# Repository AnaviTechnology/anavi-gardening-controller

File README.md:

# ANAVI Gardening Controller

Open source hardware IoT gardening controller with soil moisture sensors, I2C sensors, mini OLED SSD1306 SSD display and [Seeed Studio’s XIAO RP2040 module](https://www.seeedstudio.com/XIAO-RP2040-v1-0-p-5026.html?utm_source=github&utm_medium=ANAVI&utm_campaign=Handle) that provides a USB-C connector and a Raspberry Pi RP2040 microcontroller.

ANAVI Gardening Controller has been designed with [the cross platform and open source electronics design automation suite KiCad](https://kicad.org/).

# License

The project is released under the [Creative Commons Attribution-ShareAlike 4.0 International (CC BY-SA 4.0)](https://creativecommons.org/licenses/by-sa/4.0/).

Note: This is a human-readable summary of (and not a substitute for) the [license](https://creativecommons.org/licenses/by-sa/4.0/legalcode).

You are free to:

Share — copy and redistribute the material in any medium or format Adapt — remix, transform, and build upon the material for any purpose, even commercially. The licensor cannot revoke these freedoms as long as you follow the license terms. Under the following terms:

Attribution — You must give appropriate credit, provide a link to the license, and indicate if changes were made. You may do so in any reasonable manner, but not in any way that suggests the licensor endorses you or your use. ShareAlike — If you remix, transform, or build upon the material, you must distribute your contributions under the same license as the original. No additional restrictions — You may not apply legal terms or technological measures that legally restrict others from doing anything the license permits. Notices:

You do not have to comply with the license for elements of the material in the public domain or where your use is permitted by an applicable exception or limitation. No warranties are given. The license may not give you all of the permissions necessary for your intended use. For example, other rights such as publicity, privacy, or moral rights may limit how you use the material.

You will have to provide a link to the original creator of the project http://www.anavi.technology on any documentation or website.

Credit can be attributed through a link to the creator website: http://www.anavi.technology

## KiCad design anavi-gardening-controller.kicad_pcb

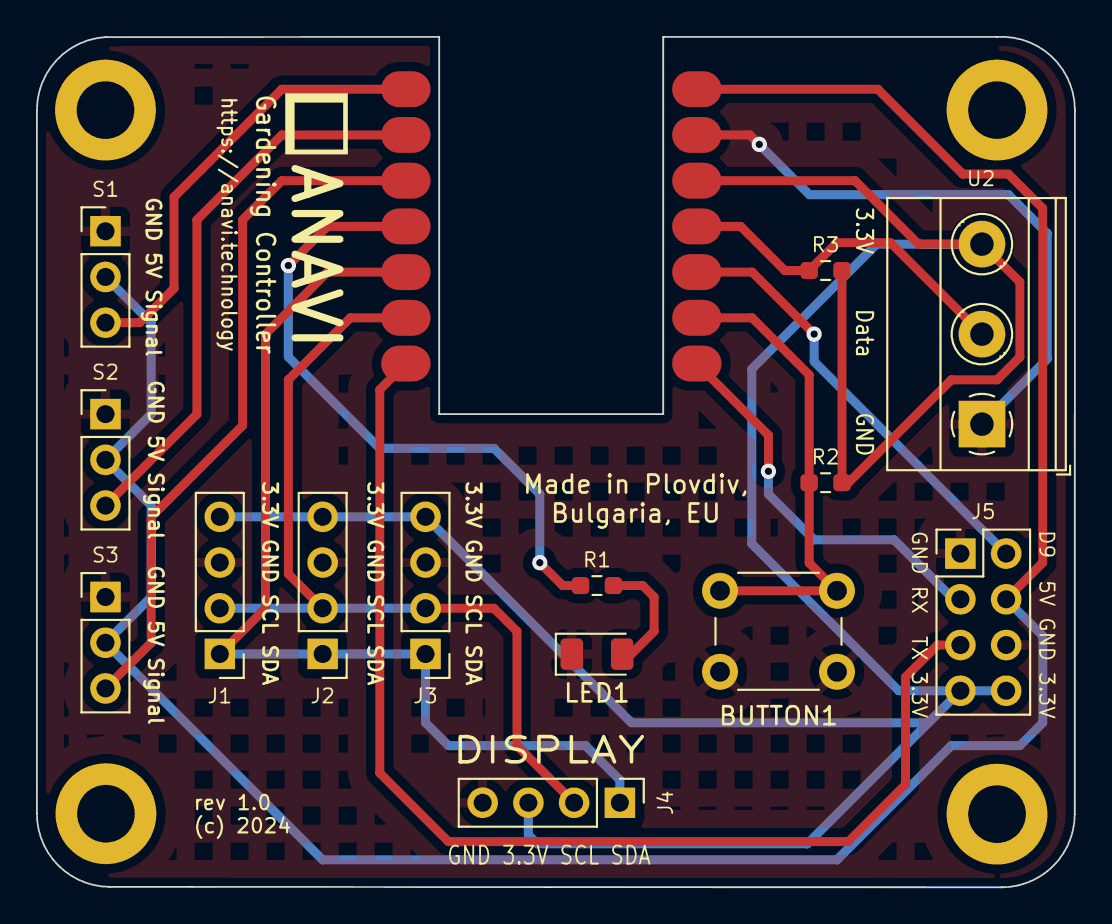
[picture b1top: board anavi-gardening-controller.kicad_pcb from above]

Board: 2 copper layers, 57.7 x 47.2 mm, 15 parts (0 on the bottom side), 15 nets.

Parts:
BUTTON1: SW_DIP_x01; SW_PUSH_6mm_H4.3mm
J1, J2, J3, J4: Conn_01x04_Female; PinHeader_1x04_P2.54mm_Vertical
J5: Conn_02x04_Odd_Even; PinHeader_2x04_P2.54mm_Vertical
LED1: KP-3216EC; LED_1206_3216Metric
R1: 68R; R_0603_1608Metric_Pad0.98x0.95mm_HandSolder
R2: 2K; R_0603_1608Metric_Pad0.98x0.95mm_HandSolder
R3: 4,7K; R_0603_1608Metric_Pad0.98x0.95mm_HandSolder
S1, S2, S3: Conn_01x03_Male; PinHeader_1x03_P2.54mm_Vertical
U1: MOUDLE-SEEEDUINO-XIAO-ESP32C3; MOUDLE14P-SMD-2.54-21X17.8MM
U2: DS18B20; TerminalBlock_Phoenix_MKDS-1,5-3_1x03_P5.00mm_Horizontal

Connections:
+3V3: J1.4, J2.4, J3.4, J4.3, J5.7, J5.8, R2.2, R3.2, U1.12 (3V3), U2.3 (VDD)
+5V: J5.4, S1.2, S2.2, S3.2, U1.14 (5V)
GND: BUTTON1.1, J1.3, J2.3, J3.3, J4.4, J5.1, J5.6, LED1.1 (K), S1.1, S2.1, S3.1, U1.13 (GND), U2.1 (GND)
unnamed: LED1.2 (A), R1.2
unnamed: J1.1, J2.1, J3.1, J4.1, U1.5 (PA8_A4_D4_SDA)
unnamed: J1.2, J2.2, J3.2, J4.2, U1.6 (PA9_A5_D5_SCL)
unnamed: R1.1, U1.4 (PA11_A3_D3)
unnamed: BUTTON1.2, R2.1, U1.9 (PA7_A8_D8_SCK)
unnamed: R3.1, U1.11 (PA6_A10_D10_MOSI), U2.2 (DQ)
unnamed: S1.3, U1.1 (PA02_A0_D0)
unnamed: S2.3, U1.2 (PA4_A1_D1)
unnamed: S3.3, U1.3 (PA10_A2_D2)
unnamed: J5.5, U1.7 (PB08_A6_D6_TX)
unnamed: J5.3, U1.8 (PB09_A7_D7_RX)
unnamed: J5.2, U1.10 (PA5_A9_D9_MISO)

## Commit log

2024-01-12 ANAVI Gardening Controller
    Initial commit
2024-01-14 Update silkscreen
    Add logo and text to the front and the back silkscreen.
2024-02-11 Adjust front and back silkscreen labels
    Adjust front and back silkscreen labels to match the direction of
    the labels on the back of XIAO ESP32C3 module.
2024-02-11 Add enclosure
    Add top and bottom parts for enclosure for ANAVI Gardening
    Controller. The enclosure is longer to cover the whole length,
    including the mini OLED display.
2024-03-02 README.md: Add details and links
    Improve the description and add details.
2024-09-14 Update to KiCad 8
    Update the project to KiCad version 8. Tested with 8.0.5 on
    Ubuntu 2024.04 LTS.
2024-09-14 assembly/anavi-gardening-controller.pdf: Add
    Add assembly diagram.

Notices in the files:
anavi-gardening-controller.kicad_pcb:
(c) 2024
